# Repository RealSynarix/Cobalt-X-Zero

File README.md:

# Cobalt-X Zero

**Open-source • 3D-printable • 50g balanced gaming mouse**

Built around the STM32G431 and PixArt PMW3360.  
No bloated software. Configuration lives entirely in the browser via WebHID.

**Config site:** [Click Me :D](https://realsynarix.github.io/Cobalt-X-Zero/)  
Works in Chrome / Edge (desktop). Plug the mouse in, hit **Connect**, create or edit profiles, save.

---

## Why this exists

Most gaming mice force you to install closed, resource-heavy software.  
Cobalt-X Zero does the opposite:

- Fully open hardware & software (PCB, shell, firmware, configurator)
- Zero host-side software required after initial flash (you need software to flash, but then you can close and optionally delete it)
- Lightweight, relatively cheap, and modifiable by design

Ideal for anyone who wants a high-performance mouse without proprietary software and host resources being hogged.

---

## Specs

| Part            | Detail                                              |
|-----------------|-----------------------------------------------------|
| **MCU**         | STM32G431KBT6 (170 MHz, LQFP-32) |
| **Sensor**      | PixArt PMW3360 |
| **Polling**     | 1000 Hz USB (8 kHz internal loop + SOF sync) |
| **Click latency**| ~2.5 ms |
| **Weight**      | 50 g (without cable) |
| **Switches**    | Kailh Mute Push Buttons (red cap, 2 pin + 10M click life-span) |
| **Wheel**       | TTC EC10 rotary encoder + custom printed wheel |
| **LEDs**        | 2× RGB (Cathode) |
| **Config**      | WebHID Github Pages Website |
| **Shell**       | Custom PETG 3D Print |

---

## Repository Layout

| Path                              | Contents                                              |
|-----------------------------------|-------------------------------------------------------|
| `firmware/`                       | C++ firmware source + pre-built binaries              |
| `hardware/fabrication/pcb/`       | KiCad project, Gerbers, BOM, position files           |
| `hardware/fabrication/shell/`     | 3D printable STLs + print settings                    |
| `docs/guides/`                    | Assembly, flashing, configuration, and general guides |

---

## Getting Started

1. **Read the docs**  
   Start with [`docs/guides/`](docs/guides/) for assembly instructions, print settings, and firmware details.

2. **Print the shell**  
   Use the STLs and recommended settings in `hardware/fabrication/shell/`.

3. **Order & assemble the PCB**  
   - Fabricate from the Gerbers in `hardware/fabrication/pcb/` (JLCPCB works well).  
   - The PMW3360 sensor must be purchased separately (e.g. AliExpress) and hand-soldered.

4. **Flash the firmware**  
   Follow the flashing guide in `docs/guides/`. Pre-built binaries are available for quick setup; source is there if you want to modify it.

5. **Configure**  
   Open the [config site](https://realsynarix.github.io/Cobalt-X-Zero/), connect the mouse, create profiles, and tune everything to your preference. Multiple profiles are supported.

---

## License & Contributions

Everything in this project is open source.  
You are free to fork, modify, improve, and share your own builds.

**Attribution is appreciated.**  
If you use Cobalt-X Zero commercially or base a project on it, please include a link back to this repository.

Issues and pull requests are always welcome.

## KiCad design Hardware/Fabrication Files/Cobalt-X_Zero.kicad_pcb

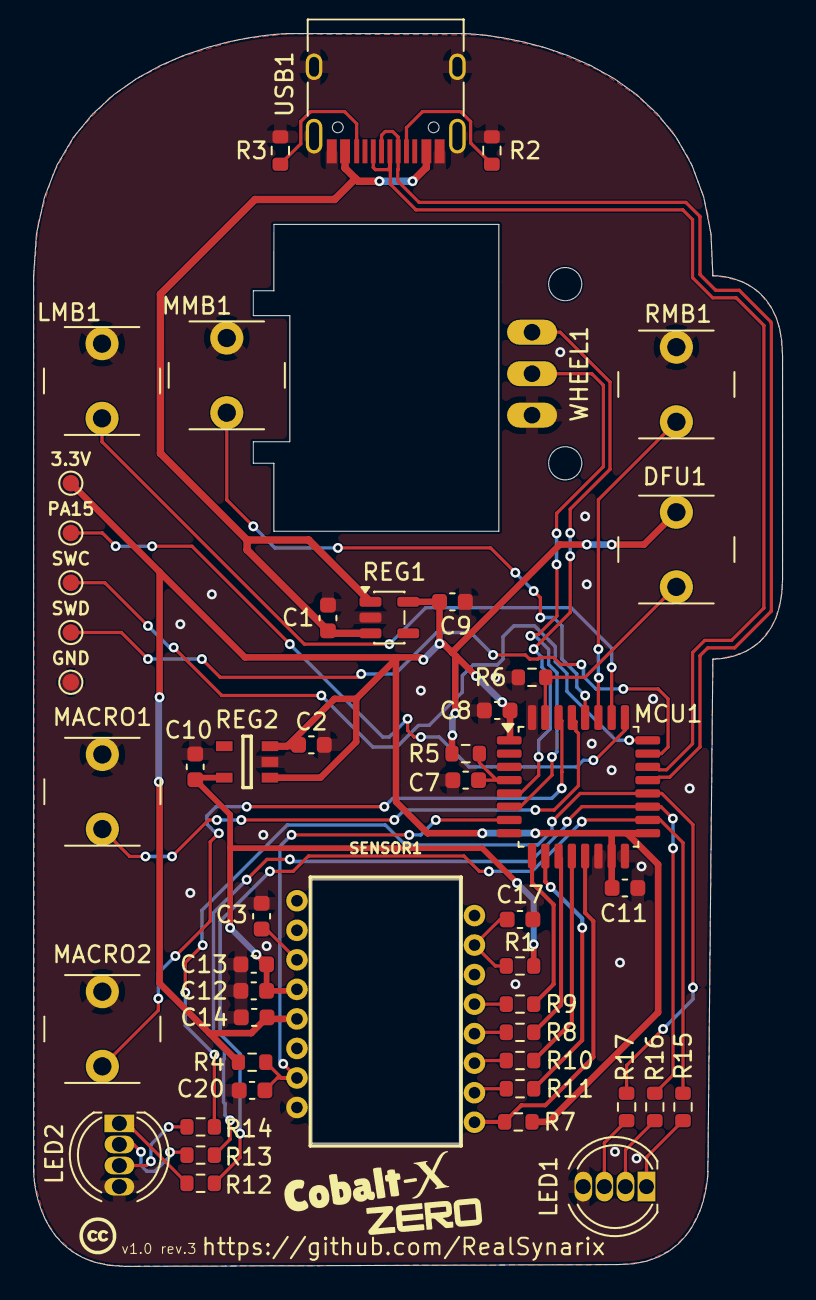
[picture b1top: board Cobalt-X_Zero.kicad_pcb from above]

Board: 2 copper layers, 45.1 x 74.3 mm, 49 parts (0 on the bottom side), 41 nets.

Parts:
3.3V: TestPoint_Probe; TestPoint_Pad_D1.0mm
C1, C2, C9, C10: 1uF; C_0603_1608Metric
C3, C17: 10nF; C_0603_1608Metric
C7, C8, C11, C12, C14, C20: 100nF; C_0603_1608Metric
C13: 4.7uF; C_0603_1608Metric
DFU1: SW_Push; SW_PUSH_6mm_H7.3mm_2-Pin
GND: TestPoint_Probe; TestPoint_Pad_D1.0mm
LED1, LED2: LED_RGBA; LED_D5.0mm-4_RGB
LMB1: SW_Push; SW_PUSH_6mm_H7.3mm_2-Pin
MACRO1, MACRO2: SW_Push; SW_PUSH_6mm_H7.3mm_2-Pin
MCU1: STM32G431KBT6; LQFP-32_7x7mm_P0.8mm
MMB1: SW_Push; SW_PUSH_6mm_H7.3mm_2-Pin
PA15: TestPoint_Probe; TestPoint_Pad_D1.0mm
R1: 39; R_0603_1608Metric
R2, R3: 5.1k; R_0603_1608Metric
R4, R5, R6: 10k; R_0603_1608Metric
R7: 100k; R_0603_1608Metric
R8, R9, R10, R11: 33; R_0603_1608Metric
R12, R13, R14, R15, R16, R17: 150; R_0603_1608Metric
REG1: AP2112K-3.3; SOT-23-5
REG2: TLV75519PDBVR; DBV0005A_N
RMB1: SW_Push; SW_PUSH_6mm_H7.3mm_2-Pin
SENSOR1: PMW3360DM-T2QU; PMW3360
SWC: TestPoint_Probe; TestPoint_Pad_D1.0mm
SWD: TestPoint_Probe; TestPoint_Pad_D1.0mm
USB1: USB_C_Receptacle_USB2.0_14P; USB_C_Receptacle_HRO_TYPE-C-31-M-12
WHEEL1: EC10E1220501; TRIM_EC10E1220501

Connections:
+1.9v: C10.1, C12.1, C13.1, R1.2, REG2.5 (OUT), SENSOR1.4 (VDD)
+3.3V: 3.3V.1 (1_1), C2.1, C8.1, C9.1, C11.1, C14.2, DFU1.2, MCU1.1 (VDD), MCU1.15 (VDDA/VREF+), MCU1.17 (VDD), R4.2, R5.2, R7.2, REG1.5 (VOUT), REG2.1 (IN), REG2.3 (EN), SENSOR1.5 (VDDIO)
+5v: C1.1, REG1.1 (VIN), REG1.3 (EN), USB1.A4 (VBUS), USB1.A9 (VBUS), USB1.B4 (VBUS), USB1.B9 (VBUS)
/BLUE: MCU1.20 (PA10), R14.1, R17.1
/BOOT0: DFU1.1, MCU1.31 (PB8-BOOT0), R6.1
/CS: MCU1.9 (PA4), R9.2
/GREEN: MCU1.19 (PA9), R13.1, R16.1
/LMB: LMB1.1, MCU1.26 (PB3)
/MAC1: MACRO1.1, MCU1.29 (PB6)
/MAC2: MACRO2.1, MCU1.30 (PB7)
/MISO: MCU1.11 (PA6), R8.2
/MMB: MCU1.28 (PB5), MMB1.1
/MOSI: MCU1.12 (PA7), R10.2
/MOTION: MCU1.13 (PB0), R7.1, SENSOR1.9 (MOTION)
/NRST: C7.1, MCU1.4 (PG10-NRST), R5.1
/PA15: MCU1.25 (PA15), PA15.1 (1_1)
/RED: MCU1.18 (PA8), R12.1, R15.1
/RMB: MCU1.27 (PB4), RMB1.1
/SCLK: MCU1.10 (PA5), R11.2
/SRST: C20.2, MCU1.7 (PA2), R4.1, SENSOR1.7 (~RESET)
/SWCLK: MCU1.24 (PA14), SWC.1 (1_1)
/SWDIO: MCU1.23 (PA13), SWD.1 (1_1)
/USB_D+: MCU1.22 (PA12), USB1.A6 (D+), USB1.B6 (D+)
/USB_D-: MCU1.21 (PA11), USB1.A7 (D-), USB1.B7 (D-)
/WHEEL_A: MCU1.5 (PA0), WHEEL1.A
/WHEEL_B: MCU1.6 (PA1), WHEEL1.B
GND: C1.2, C2.2, C3.2, C7.2, C8.2, C9.2, C10.2, C11.2, C12.2, C13.2, C14.1, C17.1, C20.1, GND.1 (1_1), LED1.4 (A), LED2.4 (A), LMB1.2, MACRO1.2, MACRO2.2, MCU1.14 (VSSA), MCU1.16 (VSS), MCU1.32 (VSS), MMB1.2, R2.2, R3.2, R6.2, REG1.2 (GND), REG2.2 (GND), RMB1.2, SENSOR1.8 (GND), USB1.A1 (GND), USB1.A12 (GND), USB1.B1 (GND), USB1.B12 (GND), USB1.S1 (SHIELD), WHEEL1.C
unnamed: LED1.3 (BK), R17.2
unnamed: LED1.2 (GK), R16.2
unnamed: LED1.1 (RK), R15.2
unnamed: LED2.3 (BK), R14.2
unnamed: LED2.2 (GK), R13.2
unnamed: LED2.1 (RK), R12.2
unnamed: C17.2, R1.1, SENSOR1.15 (LED_P)
unnamed: R8.1, SENSOR1.12 (MISO)
unnamed: R10.1, SENSOR1.11 (MOSI)
unnamed: R11.1, SENSOR1.10 (SCLK)
unnamed: C3.1, SENSOR1.3 (VDDPIX)
unnamed: R9.1, SENSOR1.13 (~CS)
unnamed: R2.1, USB1.A5 (CC1)
unnamed: R3.1, USB1.B5 (CC2)

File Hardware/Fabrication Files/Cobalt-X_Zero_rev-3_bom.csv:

Designator,Footprint,Quantity,Value,LCSC Part #
"3.3V, GND, PA15, SWC, SWD",TestPoint_Pad_D1.0mm,5,TestPoint_Probe,
"C1, C10, C2, C9",0603,4,1uF,
"C11, C12, C14, C20, C7, C8",0603,6,100nF,
C13,0603,1,4.7uF,
"C17, C3",0603,2,10nF,
"DFU1, LMB1, MACRO1, MACRO2, MMB1, RMB1",SW_PUSH_6mm_H7.3mm_2-Pin,6,SW_Push,
"LED1, LED2",LED_D5.0mm-4_RGB,2,LED_RGBA,
MCU1,LQFP-32_7x7mm_P0.8mm,1,STM32G431KBT6,
R1,0603,1,39,
"R10, R11, R8, R9",0603,4,33,
"R12, R13, R14, R15, R16, R17",0603,6,150,
"R2, R3",0603,2,5.1k,
"R4, R5, R6",0603,3,10k,
R7,0603,1,100k,
REG1,SOT-23-5,1,AP2112K-3.3,
REG2,DBV0005A_N,1,TLV75519PDBVR,
SENSOR1,PMW3360,1,PMW3360DM-T2QU,
USB1,USB_C_Receptacle_HRO_TYPE-C-31-M-12,1,USB_C_Receptacle_USB2.0_14P,
WHEEL1,TRIM_EC10E1220501,1,EC10E1220501,

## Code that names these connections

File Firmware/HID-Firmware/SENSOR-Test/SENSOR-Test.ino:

#include <Arduino.h>
#include <SPI.h>
#include <PMW3360.h>
#include <Mouse.h>
#include "system.h"
#include "usb_hid.h"

#define SENSOR_CS PA4
#define SENSOR_CPI 800

PMW3360 sensor;
static bool sensor_ok = false;

static inline int8_t clamp8(int16_t v) {
  if (v > 127) return 127;
  if (v < -127) return -127;
  return (int8_t)v;
}

void setup() {
  SystemClock_Config();
  usb_hid_init();
  delay(2000);
  pinMode(SENSOR_CS, OUTPUT);
  digitalWrite(SENSOR_CS, HIGH);
  SPI.setMOSI(PA7);
  SPI.setMISO(PA6);
  SPI.setSCLK(PA5);
  for (int i = 0; i < 10 && !sensor_ok; i++) {
    delay(200);
    sensor_ok = sensor.begin(SENSOR_CS);
  }
  if (sensor_ok) {
    sensor.setCPI(SENSOR_CPI);
    Mouse.move(20, 0, 0);
  } else {
    Mouse.move(0, 20, 0);
  }
}

void loop() {
  if (!sensor_ok) return;
  PMW3360_DATA d = sensor.readBurst();
  int8_t mx = clamp8(d.dx);
  int8_t my = clamp8(d.dy);
  if (mx != 0 || my != 0) {
    Mouse.move(mx, my, 0);
  }
}

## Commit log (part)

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2026-04-09 First git commit: working HID enumeration + button clicks (uses standard mouse lib)
2026-04-14 Added scroll wheel logic
2026-04-14 Fixed scroll increments
2026-04-14 Restructure firmware into modular HID/MSC/boot system
2026-04-14 Improved Firmware Structure
2026-04-14 Fixed HID Enumeration
2026-04-14 Added macro logic, but its scuffed
2026-04-16 Clean Codebase
2026-05-26 up-to-date codebase
